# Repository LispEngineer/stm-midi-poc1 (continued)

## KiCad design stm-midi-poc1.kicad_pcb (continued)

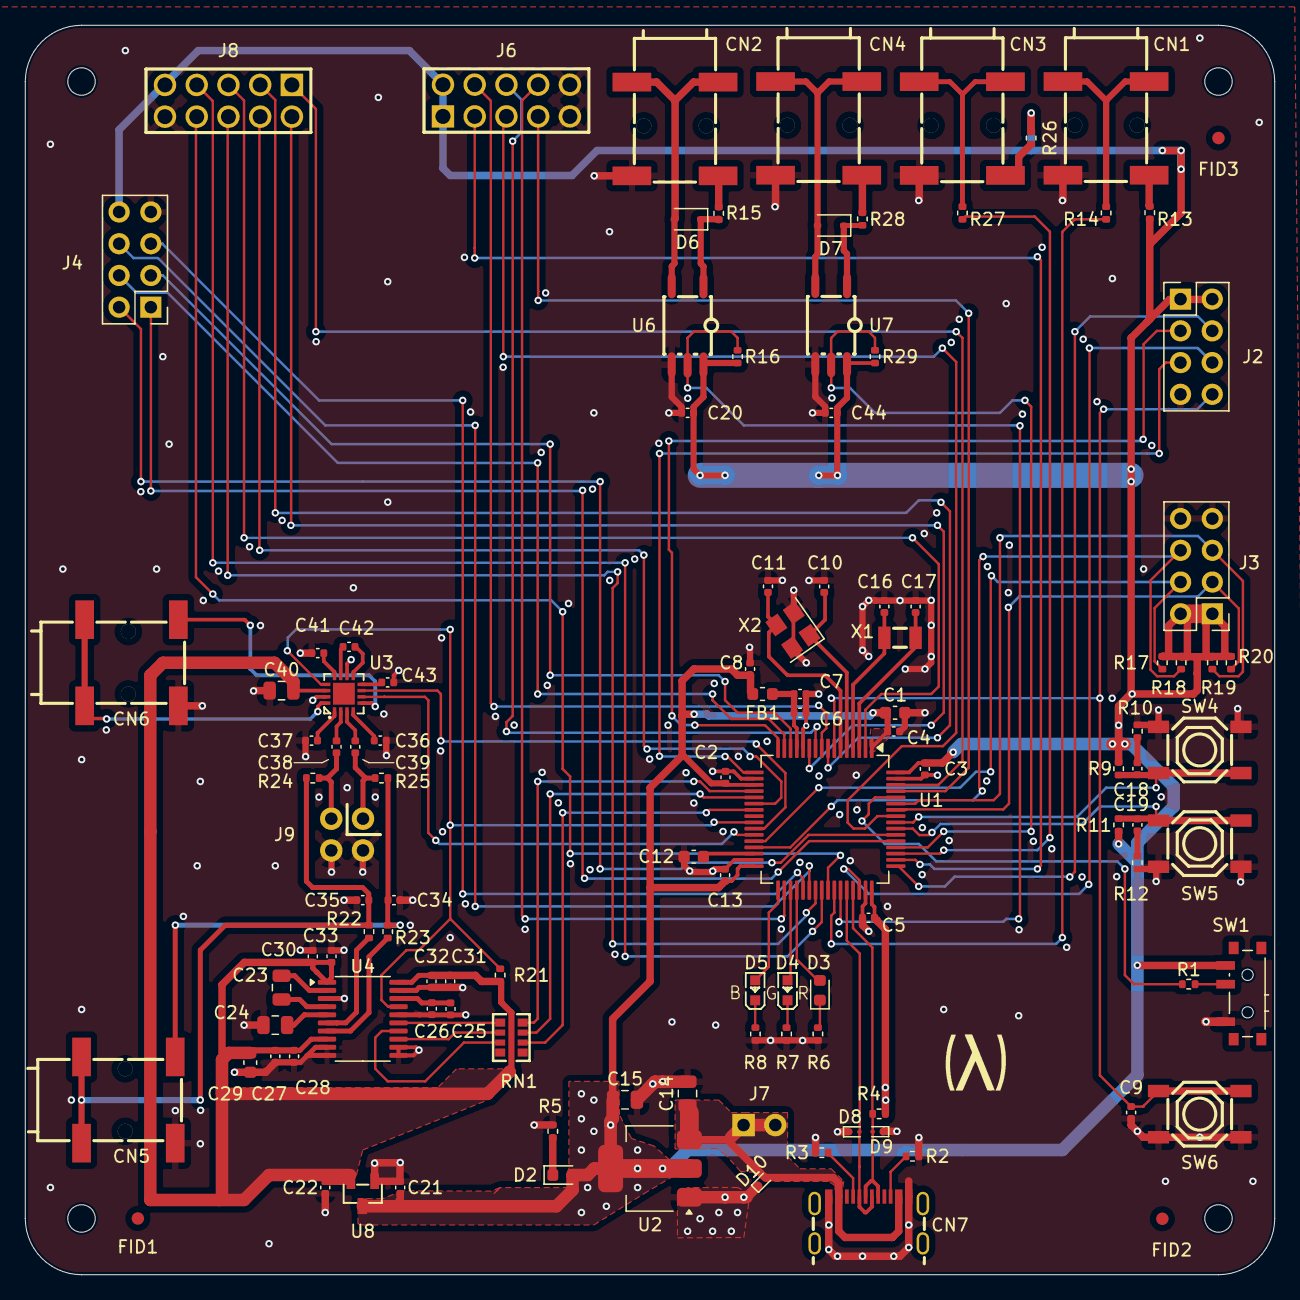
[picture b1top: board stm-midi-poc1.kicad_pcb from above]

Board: 4 copper layers, 100.0 x 100.0 mm, 118 parts (0 on the bottom side), 99 nets.

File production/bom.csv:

Designator,Footprint,Quantity,Value,LCSC Part #
"C1, C29",0603,2,10uF,C96446
"C10, C11",0402,2,10pF,C32949
C12,0603,1,4.7uF,C19666
"C13, C18, C19, C2, C20, C26, C28, C3, C32, C33, C4, C44, C5, C9",0402,14,100nF,C307331
"C14, C15",0805,2,22uF,C45783
"C16, C17",0402,2,4.7pF,C1569
"C21, C22, C25, C27, C30, C31, C36, C37, C38, C39, C41, C42, C43, C7, C8",0402,15,1uF,C52923
"C23, C24, C40",0805,3,2.2uF,C377773
"C34, C35, C6",0402,3,10nF,C15195
CN1,AUDIO-SMD_PJ-321A-4A,1,MIDI Out 1,C879743
CN2,AUDIO-SMD_PJ-321A-4A,1,MIDI In 1,C879743
CN3,AUDIO-SMD_PJ-321A-4A,1,MIDI Out 2,C879743
CN4,AUDIO-SMD_PJ-321A-4A,1,MIDI In 2,C879743
CN5,AUDIO-SMD_PJ-321A-4A,1,Line out,C879743
CN6,AUDIO-SMD_PJ-321A-4A,1,Headphone,C879743
"D10, D8, D9",D_SOD-923,3,ESD,C111566
D2,0603,1,RED_PWR,C2286
D3,0603,1,USER_RED,C2286
D4,0603,1,USER_GREEN,C72043
D5,0603,1,USER_BLUE,C72038
"D6, D7",D_SOD-123,2,1N4148W,C81598
FB1,0603,1,120@100MHz,C133937
J1,USB-C-SMD_GT-USB-7010I,1,GT-USB-7010I,C5362630
J2,PinHeader_1x05_P2.54mm_Vertical,1,SWD,C7430361
J3,PinHeader_2x04_P2.54mm_Vertical,1,I2C,C5156676
J4,PinHeader_2x04_P2.54mm_Vertical,1,UART46,C5156676
J5,PinHeader_1x04_P2.54mm_Vertical,1,UART5,C5116483
J6,PinHeader_1x05_P2.54mm_Vertical,1,SPI,C7430361
J9,PinHeader_1x04_P2.54mm_Vertical,1,Serial,C5116483
P1,HDR-TH_16P-P2.54-V-M-R2-C8-S2.54,1,GPIO,C68234
"R1, R21",0402,2,10kΩ,C25744
"R10, R12",0402,2,100Ω,C25076
"R11, R9",0402,2,4k7Ω,C25900
"R13, R14, R26, R27",0402,4,47Ω,C25118
"R15, R22, R23, R28",0402,4,220Ω,C25091
"R16, R29",0402,2,470Ω,C25117
"R17, R18, R19, R20",0402,4,1k8Ω,C25871
"R2, R3",0402,2,5k1Ω,C25905
"R24, R25",0402,2,3k9Ω 1%,C51721
"R4, R5, R6, R7, R8",0402,5,1k5Ω,C25867
RN1,RES-ARRAY-SMD_0603-8P-L3.2-W1.6-BL,1,56Ω,C25512
SW1,SW_SPDT_PCM12,1,BOOT0,C109335
SW2,SW_SPDT_PCM12,1,Gain0,C109335
SW3,SW_SPDT_PCM12,1,Gain1,C109335
SW4,SW-SMD_4P-L5.1-W5.1-P3.70-LS6.5-TL-2,1,BTN1,C318884
SW5,SW-SMD_4P-L5.1-W5.1-P3.70-LS6.5-TL-2,1,BTN2,C318884
SW6,SW-SMD_4P-L5.1-W5.1-P3.70-LS6.5-TL-2,1,Reset,C318884
U1,LQFP-64_10x10mm_P0.5mm,1,STM32F722RETx,C118207
U2,SOT-223-3_TabPin2,1,AMS1117-3.3,C6186
U3,QFN-16_L3.0-W3.0-P0.50-BL-EP1.7,1,PAM8908JER,C33233
U4,TSSOP-20_4.4x6.5mm_P0.65mm,1,PCM5102A,C107671
"U6, U7",SOP-8_L9.8-W6.6-P2.54-LS10.3-BL,2,6N137S-TA1,C92651
U8,SOT-23-3_L2.9-W1.3-P1.90-LS2.4-BR,1,AP7333-33SRG-7,C150745
X1,FC-135R_L3.2-W1.5,1,32.768kHz 7pF,C48615
Y1,Crystal_SMD_3225-4Pin_3.2x2.5mm,1,16MHz 10pF,C112972

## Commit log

2024-09-28 Updated schematic PDF
2024-10-06 Updated schematic with parts found in JLCPCB parts database. Updated footprints, 3d models for those items. All schematic symbols now have LCSC part numbers, footprints and 3D models. No PCB layout h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
2024-10-06 Update PDF of schematic. Add (bad) PDF of PCB and 3D image of PCB. (Remember: PCB is not designed/started yet.)
2024-10-06 Move related PCB components near each other in preparation of PCB layout.
2024-10-07 Group PCB components together more. Replace 2x2x4 by 1x2x8 connector.
2024-10-12 Create PCB outline and move components into better locations. (Not done yet!) Update schematic a little bit with additional nets and clarifications. Add mounting holes. Unify components/footprints.
2024-10-12 Ready to start routing the PCB I think
2024-10-12 Connected all power for Decoupling Caps
2024-10-12 Connected the two crystals
2024-10-12 Work on power section and some miscellaneous small areas
2024-10-12 Routed USB data lines; revised USB ESD for 2-layer board.
2024-10-12 Modify power to analog side.
2024-10-12 Wire in headphone jack with 0-ohm
2024-10-14 Audio section is completely routed.
2024-10-14 Routed the SWD. I don't think it will be possible to do this on a 2-layer board anymore. I already had to use several 0-ohm resistors.
2024-10-14 Added KiCAD Design Rules from https://github.com/labtroll/KiCad-DesignRules
2024-10-14 Added constraints from JLCPCB to the settings.
2024-10-14 Updates to clear DRC checker errors.
2024-10-14 Move to 4 layer board; no other changes. S/G/S/G Top to Bottom.
2024-10-14 Start routing through the new signal layer.
2024-10-14 Amateur hour. Routed all power and SPI, I2C, MIDI. Left GPIO and UARTs undone. Probably need to restart from scratch.
2024-10-14 Routed power to the GPIO/I2C
2024-10-19 Removed all vias/tracks and moved signal layers to outside for this EVT board design
2024-10-19 Routed all decoupling caps on top layer, as well as USB power input.
2024-10-20 Routed clock signals and addded GND guard.
2024-10-20 Routed USB signals.
2024-10-20 Routed DAC digital signals
2024-10-20 Added GND routing for DAC, USB, power areas
2024-10-20 Routed Headphone Amplifier
2024-10-20 Routed MIDI
2024-10-20 Routed SPI
2024-10-20 Routed SWD
2024-10-20 WIP: Routing SPI
2024-10-20 Routed I²C (previous commit was WIP for I²C as well)
2024-10-20 Routed Reset & Boot0
2024-10-20 Routed audio power and misc.
2024-10-20 Routed UART4 - may need to be changed for its pinout
2024-10-25 All signals now routed through revised GPIO pinout. TODO: Put ground vias everywhere needed for signal vias.
2024-10-25 All power now routed. TODO: Fix all DRC warnings
2024-10-25 All PCB DRC rule errors fixed.
2024-10-25 All important DRC warnings addressed. Others ignored. Check against Schematic complete.
2024-10-25 Rotate all silkscreen up. Move all silkscreen off vias. Misc cleanups.
2024-10-25 More cleanups.
2024-10-25 Added ground fill to both signal layers, including vias where empty islands formed.
2024-10-25 Added rear silk screen labels
2024-10-25 Added logo silk screen/footprint, exported some files (not final)
2024-10-26 1. Update README with info on my KiCAD component library. 2. Add Fiducial markers. 3. Add LCSC IDs for all parts in BOM.
2024-10-26 1. Remove unused components on schematic. 2. Find other color LEDs in JLCPCB.
2024-10-26 Found an in-stock blue LED but it is expensive.
2024-10-26 Trying to get things ready for sending to JLCPCB
2024-10-27 Reviewing every item in the BOM against LCSC database. Found several errors already. Part way done.
2024-10-27 Finished checking all parts against LCSC IDs. Found remaining errors. Added manufacturer part numbers to all parts.
2024-10-27 Regenerated JLCPCB exports using JLCPCB Tools 2024.10.01
2024-10-27 Created Gerber files using 'gerber to order' plugin 1.0.6
2024-10-27 Created production files using Fabrication Toolkit plugin 4.5.0
2024-10-27 Updated board assembly PDF using Board2Pdf 1.7.2
2024-10-27 Generated interactive HTML BOM using InteractiveHtmlBom v2.9.0 plugin
2024-10-27 Some new notes for README
2024-10-27 Updated Schematic as PDF
2024-10-27 Remove outdated PCB PDF - see the one in plots directory
2024-11-01 Add details of production run 1. Move design document into repo.
2024-11-01 Update README with link to software repos
2024-11-01 Part finder.
2024-11-02 Added myriad netclasses and set colors for them.
2024-11-02 Update schematic with notes on the headphone amplifier and I2S MCK
2024-11-02 More details on smaller optoisolators
2024-11-06 Received EVT #1 boards. Updating based on errors found so far. Added revision page. First error was misunderstanding the TRS connector pinout/schematic.
2024-11-06 1. Fixed mis-wired 3.5mm jacks everywhere. 2. Use smaller opto-isolator and diode with updated circuit for one MIDI.
2024-11-06 Cleanup tracks & vias
2024-11-07 Move MIDI1 to the new opto-isolator circuit. Update silkscreen with EVT#2.
2024-11-07 Continued additional minor cleanups
2024-11-07 Found a TLP2362 replacement: ISOM8710
2024-11-08 Stock notice
2024-11-10 Add 5V test pins
2024-11-13 Update some TODOs
2024-11-15 Added front picture
2024-11-15 Annotate picture.
2024-11-24 Add key documentation references
2024-12-21 More revisions for EVT2: 1. Move GAIN0/1 to MCU pins. 2. Revise SPI header with additional screen GPIO. 3. Revise GPIO header due to 1 and 2.
2024-12-21 Correct 3D positioning of 2-pin header
2024-12-21 Update schematic date and minor reposition of GND vias
2024-12-21 Consolidate USART2 Console with SWD debug header
2024-12-21 Consolidate UART5 with 4 & 6 on a single header
2024-12-21 Update derived documents from latest changes
2024-12-21 Misc cleanups: Consistent part designators, move and clean silkscreen, etc.
2024-12-22 Add female jumper to allow experimenting with Pimoroni circuit (default 1kΩ). Minor cleanups.
2024-12-22 Prepare EVT2 for JLCPCB by replacing parts not in stock and generating necessary outputs.
2024-12-22 EVT2 submitted to JLCPCB
2024-12-22 Notes about JLCPCB KiCAD plugins
2025-01-04 Received EVT #2 boards. Testing so far reveals no problems.
2025-01-21 Update README with more TODOs
2025-04-20 Use J-Link. FTDI notes
